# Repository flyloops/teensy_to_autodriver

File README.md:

# teensy_to_autodriver
A simple PCB for connecting the Teensy3.2 to the Sparkfun Autodriver.  

* [Schematic (PDF)](teensy_to_autodriver.pdf)
* [Bill-of-material](BOM.txt)

# Top View: 

# Bottom View:

# License: 
Creative Commons Attribution 4.0 International CC BY 4.0

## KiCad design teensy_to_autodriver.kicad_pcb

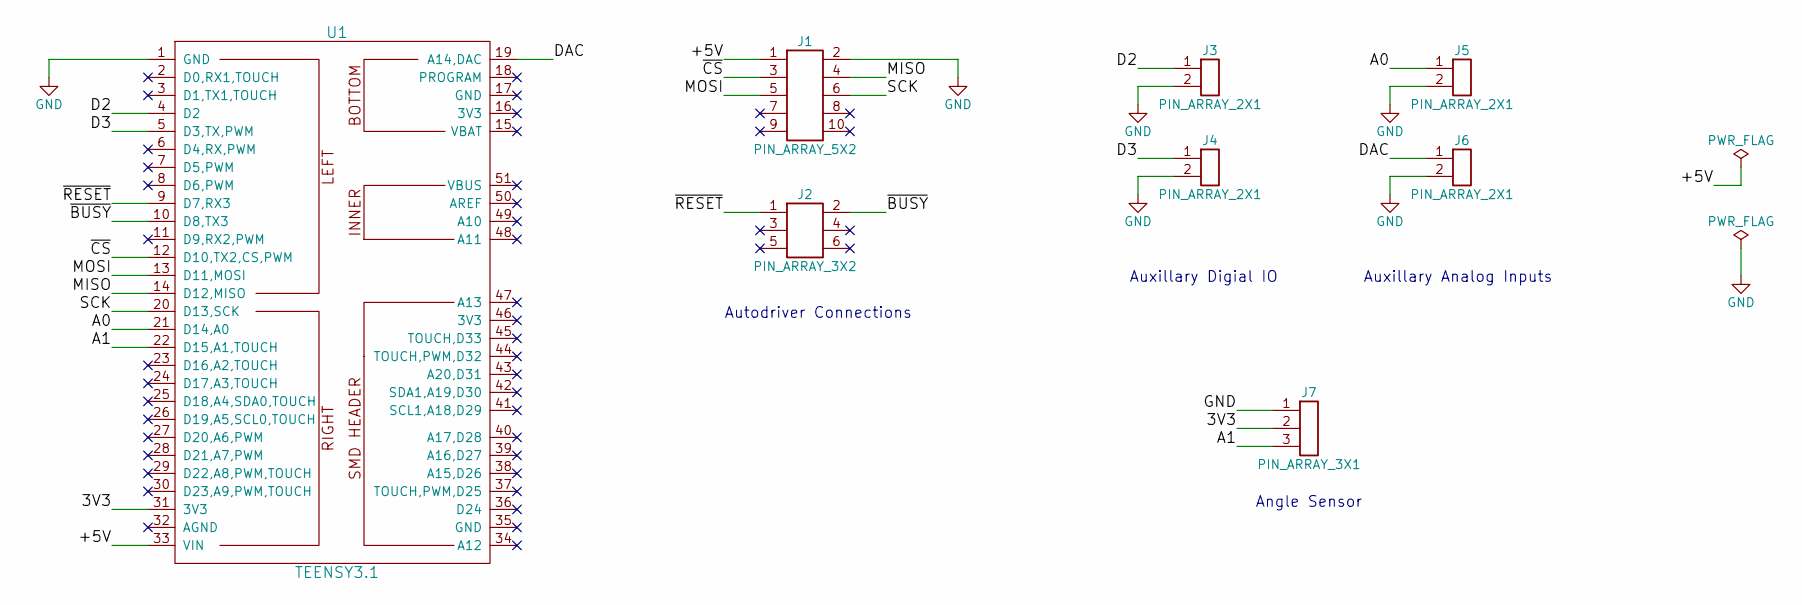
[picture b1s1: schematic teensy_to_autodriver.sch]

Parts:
J1: PIN_ARRAY_5X2; 5X2_SHRD_HEADER
J2: PIN_ARRAY_3X2; 3X2_SHRD_HEADER
J3, J4, J5, J6: PIN_ARRAY_2X1; BNC
J7: PIN_ARRAY_3X1; HEADER_3X1
U1: TEENSY3.1; TEENSY3X

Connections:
/3V3: J7.2, U1.31 (3V3)
/+5V: J1.1, U1.33 (VIN)
/A0: J5.1, U1.21 (D14,A0)
/A1: J7.3, U1.22 (D15,A1,TOUCH)
/D2: J3.1, U1.4 (D2)
/D3: J4.1, U1.5 (D3,TX,PWM)
/DAC: J6.1, U1.19 (A14,DAC)
/MISO: J1.4, U1.14 (D12,MISO)
/MOSI: J1.5, U1.13 (D11,MOSI)
/SCK: J1.6, U1.20 (D13,SCK)
/~BUSY: J2.2, U1.10 (D8,TX3)
/~CS: J1.3, U1.12 (D10,TX2,CS,PWM)
/~RESET: J2.1, U1.9 (D7,RX3)
GND: J1.2, J3.2, J4.2, J5.2, J6.2, J7.1, U1.1 (GND)

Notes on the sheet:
Autodriver Connections
Auxillary Digial IO
Auxillary Analog Inputs
Angle Sensor

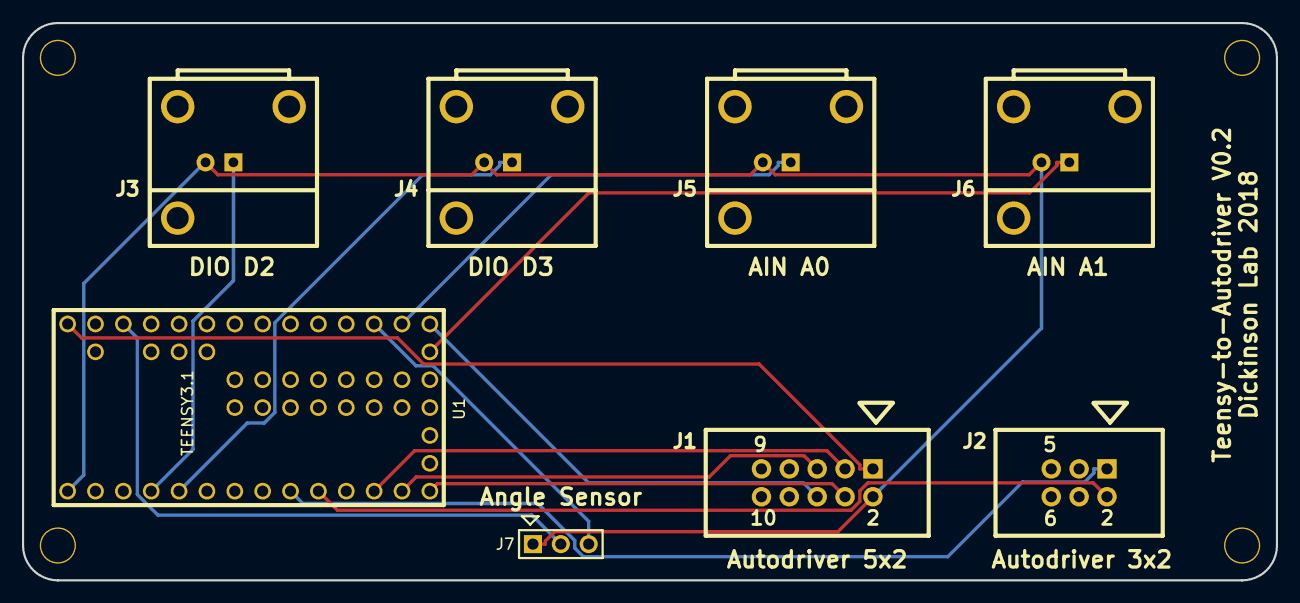
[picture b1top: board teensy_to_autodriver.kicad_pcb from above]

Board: 2 copper layers, 114.3 x 50.8 mm, 12 parts (0 on the bottom side), 14 nets.

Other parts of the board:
M0, M1, M2, M3: VAL**; MOUNT_HOLE_4_40

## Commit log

2018-01-11 Project creation.
2018-01-11 Create README.md
    Added Readme with top and bottom views of PCB.
2018-01-17 Created version 0.2 of design. Added header for angle sensor.
2018-01-17 Added pdf of schematic.
2018-01-17 Added link to schematic in README.
2018-01-17 Added bill-of-materials and link to it in the README.
2019-05-28 Added OSH Park link.
